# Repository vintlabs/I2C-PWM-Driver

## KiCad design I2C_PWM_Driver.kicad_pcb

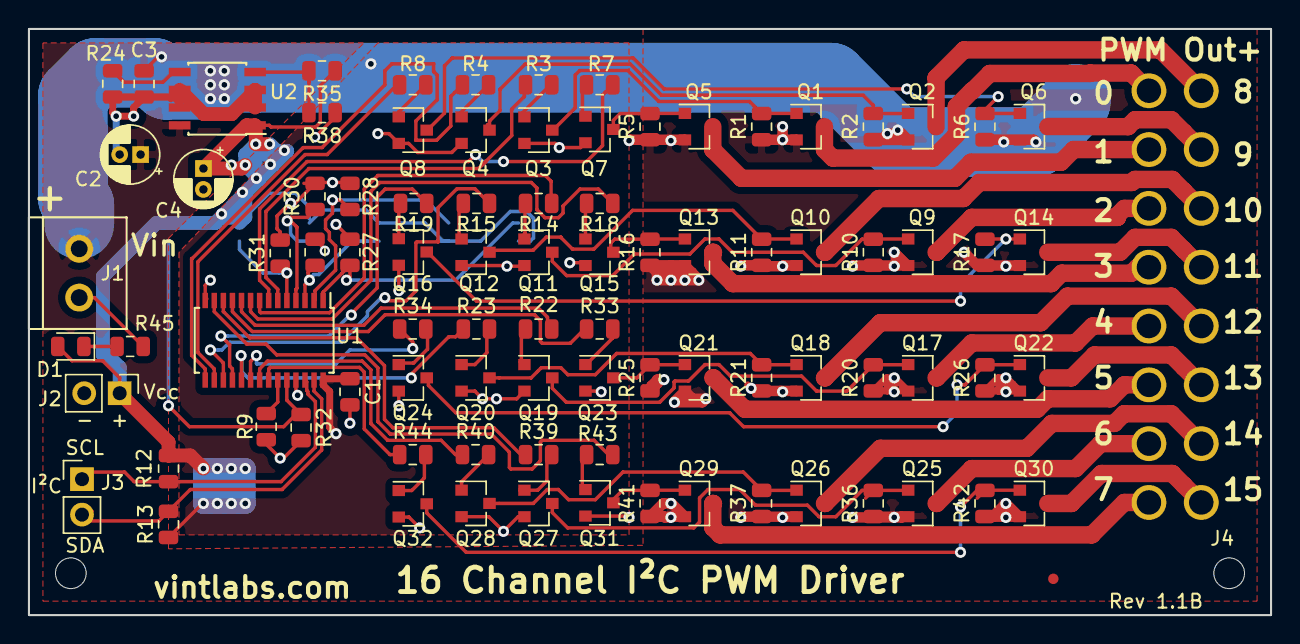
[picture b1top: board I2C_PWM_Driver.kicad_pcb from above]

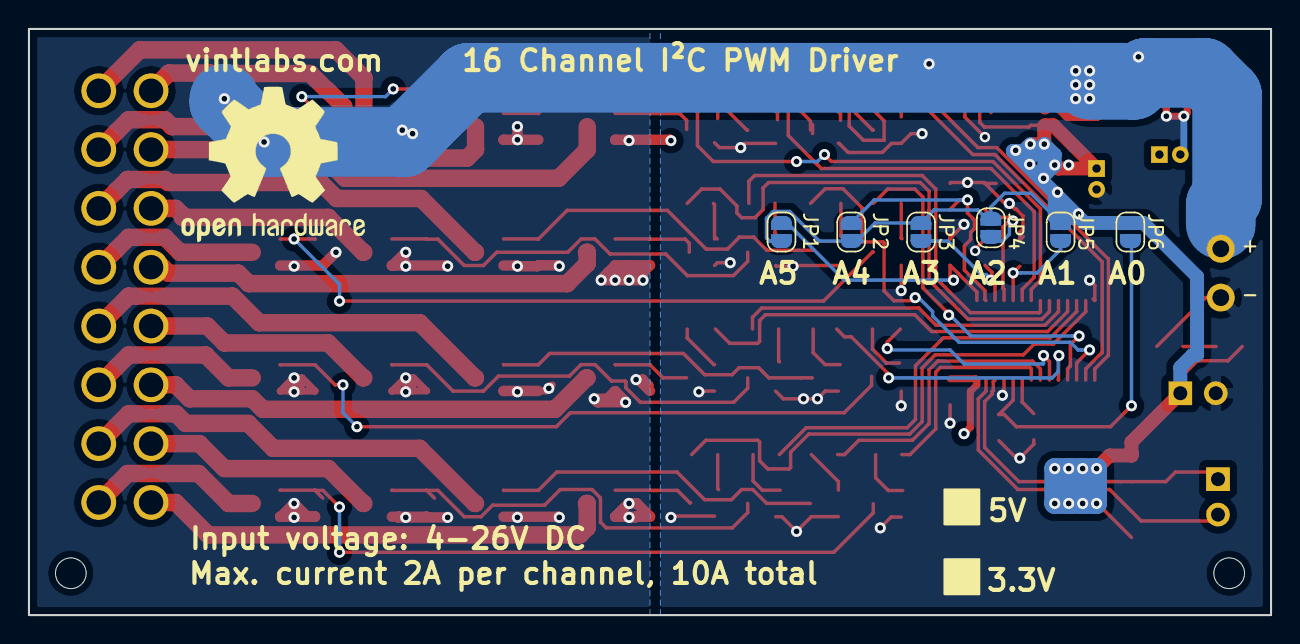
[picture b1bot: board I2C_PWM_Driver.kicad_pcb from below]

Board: 2 copper layers, 89.0 x 42.0 mm, 94 parts (6 on the bottom side), 79 nets.

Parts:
C1, C3: 0.1u; C_0805_2012Metric
C2: 1u; CP_Radial_D4.0mm_P1.50mm
C4: 100u; CP_Radial_D4.0mm_P1.50mm
D1: LED; LED_0805_2012Metric
J1: Screw_Terminal_01x02; SCREW TERMINAL BLOCK 3.5MM 2POS
J2: Conn_01x02_Male; PinHeader_1x02_P2.54mm_Vertical
J3: Screw_Terminal_01x02; PinHeader_1x02_P2.54mm_Vertical
J4: Conn_02x08_Odd_Even; PWM_Wire_Conn
JP1, JP2, JP3, JP4, JP5, JP6: SolderJumper_2_Open; SolderJumper-2_P1.3mm_Open_RoundedPad1.0x1.5mm
Q1, Q2, Q5, Q6, Q9, Q10, Q13, Q14, Q17, Q18, Q21, Q22, Q25, Q26, Q29, Q30: DMG2305UX; SOT-23
Q3, Q4, Q7, Q8, Q11, Q12, Q15, Q16, Q19, Q20, Q23, Q24, Q27, Q28, Q31, Q32: BC817; SOT-23
R1, R2, R5, R6, R10, R11, R16, R17, R20, R21, R25, R26, R36, R37, R41, R42, R45: 1k; R_0805_2012Metric
R3, R4, R7, R8, R9, R12, R13, R14, R15, R18, R19, R22, R23, R24, R27, R28, R29, R30, R31, R32, R33, R34, R39, R40, R43, R44: 10k; R_0805_2012Metric
R35: 22k; R_0805_2012Metric
R38: 39k; R_0805_2012Metric
U1: PCA9685PW; TSSOP-28_4.4x9.7mm_P0.65mm
U2: LM2931-5.0_SO8; SOIC-8_3.9x4.9mm_P1.27mm

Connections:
+VDC: C2.1, C3.1, J1.1, Q1.2, Q2.2, Q5.2, Q6.2, Q9.2, Q10.2, Q13.2, Q14.2, Q17.2, Q18.2, Q21.2, Q22.2, Q25.2, Q26.2, Q29.2, Q30.2, R1.1, R2.1, R5.1, R6.1, R10.1, R11.1, R16.1, R17.1, R20.1, R21.1, R25.1, R26.1, R36.1, R37.1, R41.1, R42.1, U2.8
A0: JP1.2, R27.1, U1.1
A1: JP2.2, R28.1, U1.2
A2: JP3.2, R29.1, U1.3
A3: JP4.2, R30.1, U1.4
A4: JP5.2, R31.1, U1.5
A5: JP6.2, R32.1, U1.24
GND: C1.2, C2.2, C3.2, C4.2, J1.2, J2.2, Q3.2, Q4.2, Q7.2, Q8.2, Q11.2, Q12.2, Q15.2, Q16.2, Q19.2, Q20.2, Q23.2, Q24.2, Q27.2, Q28.2, Q31.2, Q32.2, R9.2, R24.2, R27.2, R28.2, R29.2, R30.2, R31.2, R32.2, R38.1, R45.2, U1.14, U1.25, U2.2, U2.3, U2.6, U2.7
unnamed: D1.1, R45.1
unnamed: Q1.1, Q3.3, R1.2
unnamed: Q2.1, Q4.3, R2.2
unnamed: Q3.1, R3.2
unnamed: Q4.1, R4.2
unnamed: Q5.1, Q7.3, R5.2
unnamed: Q6.1, Q8.3, R6.2
unnamed: Q7.1, R7.2
unnamed: Q8.1, R8.2
unnamed: Q10.1, Q12.3, R11.2
unnamed: Q11.1, R14.2
unnamed: Q9.1, Q11.3, R10.2
unnamed: Q12.1, R15.2
unnamed: Q13.1, Q15.3, R16.2
unnamed: Q14.1, Q16.3, R17.2
unnamed: Q15.1, R18.2
unnamed: Q16.1, R19.2
unnamed: Q17.1, Q19.3, R20.2
unnamed: Q18.1, Q20.3, R21.2
unnamed: Q19.1, R22.2
unnamed: Q20.1, R23.2
unnamed: Q21.1, Q23.3, R25.2
unnamed: Q22.1, Q24.3, R26.2
unnamed: Q23.1, R33.2
unnamed: Q24.1, R34.2
unnamed: Q25.1, Q27.3, R36.2
unnamed: Q26.1, Q28.3, R37.2
unnamed: Q27.1, R39.2
unnamed: Q28.1, R40.2
unnamed: Q29.1, Q31.3, R41.2
unnamed: Q30.1, Q32.3, R42.2
unnamed: Q31.1, R43.2
unnamed: Q32.1, R44.2
unnamed: R9.1, U1.23
unnamed: R24.1, U2.5
unnamed: R35.2, R38.2, U2.4
Out0: J4.1, Q1.3
Out1: J4.2, Q5.3
Out2: J4.3, Q9.3
Out3: J4.4, Q13.3
Out4: J4.5, Q17.3
Out5: J4.6, Q21.3
Out6: J4.7, Q25.3
Out7: J4.8, Q29.3
Out8: J4.9, Q2.3
Out9: J4.10, Q6.3
Out10: J4.11, Q10.3
Out11: J4.12, Q14.3
Out12: J4.13, Q18.3
Out13: J4.14, Q22.3
Out14: J4.15, Q26.3
Out15: J4.16, Q30.3
SCL: J3.1, R12.2, U1.26
SDA: J3.2, R13.2, U1.27
Sig0: R3.1, U1.6
Sig1: R7.1, U1.7
Sig2: R14.1, U1.8
Sig3: R18.1, U1.9
Sig4: R22.1, U1.10
Sig5: R33.1, U1.11
Sig6: R39.1, U1.12
Sig7: R43.1, U1.13
Sig8: R4.1, U1.15
Sig9: R8.1, U1.16
Sig10: R15.1, U1.17
Sig11: R19.1, U1.18
Sig12: R23.1, U1.19
Sig13: R34.1, U1.20
Sig14: R40.1, U1.21
Sig15: R44.1, U1.22
VCC: C1.1, C4.1, D1.2, J2.1, JP1.1, JP2.1, JP3.1, JP4.1, JP5.1, JP6.1, R12.1, R13.1, R35.1, U1.28, U2.1

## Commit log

2019-01-30 Added schematic PDF
2020-01-17 Updated resistor valuesUpdated resistor valuesUpdated resistor valuesUpdated resistor values
2020-01-17 Removed SW1 (reset - never used)
2020-01-19 Routing complete (pending audit)
2020-01-20 Silk updates
2020-01-20 Minmor silk updates
2020-01-28 Fixed reversed SDA/SCL
